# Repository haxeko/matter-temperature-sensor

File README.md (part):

# TH-SENSOR-H2 — nhiệt ẩm kế Matter over Thread (ESP32-H2, 1 × CR2450)

Thiết kế firmware và phần cứng (Rev B) cho một nhiệt ẩm kế không màn hình:

- module **ESP32-H2-MINI-1-H4S** (4 MB flash, anten PCB), **Matter over Thread** (Sleepy End Device, ICD SIT), BLE chỉ dùng khi commissioning;
- cảm biến **SHT40-AD1B-R3** trên một "lưỡi" PCB tách nhiệt, đo mỗi 60 s;
- nguồn **1 × CR2450** (holder SMT): P-MOSFET chống ngược cực, một bộ buck-boost TPS63900 ra 3.3 V, tụ đệm đầu vào 10 µF + 2 × 100 µF + 470 µF;
- một nút USER, một nút RST, một LED; không màn hình.

Firmware dùng ESP-IDF thuần (ESP-Matter chính thức, FreeRTOS, `i2c_master`, ADC có hiệu chuẩn, NVS, power management). PCB là KiCad 9 gốc, 2 lớp, 41.5 × 57.5 mm, sinh hoàn toàn bằng script trong `hardware/scripts/`.

Rev B thay Rev A (2 × CR2032, bo 72 × 58 mm) theo yêu cầu chỉ dùng một pin và bo gọn hơn; Rev A còn trong lịch sử git. Lý do chọn CR2450 thay vì một CR2032: `docs/decisions.md` D20.

Biến thể **TH-SENSOR-H2C Rev A** dùng **chip ESP32-H2FH4S rời** (QFN32) thay cho module: thạch anh 32 MHz, mạng phối hợp RF 0201, **ăng-ten in trên PCB** (inverted-F theo TI DN007), **PCB 4 lớp**, cùng kích thước bo, cùng đường nguồn và cùng firmware. File ở `hardware/chip/`, mô tả và giới hạn ở `docs/chip_variant.md`. Phần RF của biến thể này chưa đo và chưa chỉnh.

Biến thể **TH-SENSOR-H2W Rev A** dùng **module ESP32-H2-WROOM-02C-H4S** (người dùng tự mua và hàn, không có trong BOM JLC) trên một **bo 4 lớp vuông 37.6 × 37.6 mm tính cả phần ăng-ten của module nhô ra ngoài mép trên** (bo 37.6 × 31.6 mm); holder CR2450 ở mặt dưới, tụ đệm C5 là tụ tantal thấp nên cả cụm cao ≈ 12.3 mm (ước tính), một nút USER/BOOT bấm cạnh ở giữa mép trái (không có nút RST), J1 là 6 pad dán; gắn tường với cạnh có nút quay xuống đất (nút bấm từ dưới lên, lưỡi cảm biến ở góc dưới); mạch nguồn, cảm biến và firmware như Rev B. File ở `hardware/wroom/`, mô tả và giới hạn ở `docs/wroom_variant.md`.

Biến thể **TH-SENSOR-H2W-123 Rev A** là bo H2W chạy bằng **một pin CR123A** (1550 mAh) thay cho CR2450. Pin **không nằm trên bo**: bo chỉ mang phần mạch, **2 lớp**, **24.8 × 37.3 mm** (43.3 mm tính cả ăng-ten), pin đặt cạnh bo trong đế riêng và nối bằng hai dây; đặt cạnh một đế pin 18.2 × 43.3 mm thì cả cụm khoảng 43.3 × 43.3 mm. Không có tụ đệm 470 µF, có cầu chì tự phục hồi; pad nạp và test pad ở mặt sau; gắn tường với ăng-ten hướng lên, cảm biến và nút ở cạnh dưới. Theo mô hình (ƯỚC TÍNH), pin này cấp được mọi xung tải ở mọi trạng thái và cho tuổi thọ khoảng 2.3–2.6 năm. Pin sát bo chỉ cách ăng-ten khoảng 7 mm: tầm phủ CHƯA KIỂM THỬ. Chi tiết: `docs/cr123a_variant.md`.

## Trạng thái — đọc trước

Nhãn dùng trong toàn bộ repo: **ĐÃ XÁC MINH** (kiểm bằng công cụ hoặc đọc từ tài liệu gốc), **ƯỚC TÍNH** (tính toán/mô phỏng), **CHƯA KIỂM THỬ** (chưa có phần cứng).

| Hạng mục | Trạng thái | Bằng chứng |
|---|---|---|
| Firmware build: `battery`, `debug`, `battery` + lớp phủ sản xuất `prod`, `battery` + `cr123a`, `debug` + `cr123a` | ĐÃ XÁC MINH (ESP-IDF v5.5.5, 0 cảnh báo trong mã dự án; lần 2026-10-30 build sạch từ bản clone, lần 2026-11-11 build lại toàn bộ trong cây làm việc) | `docs/reports/firmware_build.md` |
| Firmware chạy trên chip (mọi profile; prod còn cần dữ liệu factory riêng từng máy) | **CHƯA KIỂM THỬ** | `docs/test_plan.md` |
| Unit test logic thuần trên host | ĐÃ XÁC MINH: 43 test, 264 kiểm tra, 0 lỗi | `docs/reports/host_tests.txt` |
| ERC schematic | ĐÃ XÁC MINH: 0 lỗi, 0 cảnh báo | `hardware/reports/erc_report.txt` |
| DRC PCB + schematic parity | ĐÃ XÁC MINH: 0 vi phạm, 0 pad chưa nối, 0 lỗi parity | `hardware/reports/drc_report.txt` |
| Pin map firmware ↔ schematic | ĐÃ XÁC MINH | `tools/check_pinmap.py`, `docs/pinmap.md` |
| Gerber, drill, BOM, CPL (định dạng JLC) | ĐÃ XÁC MINH là sinh được từ board; **chưa gửi nhà máy** | `hardware/production/` |
| Năng lượng, tuổi thọ pin | ƯỚC TÍNH — **CHƯA ĐẠT** | `docs/power_budget.md` |
| Điện, RF, cảm biến, Matter, dòng ngủ trên bo thật | **CHƯA KIỂM THỬ** (chưa có bo nào được làm) | `docs/test_plan.md` |
| OTA | **không triển khai** (`CONFIG_ENABLE_OTA_REQUESTOR=n`) | |
| Chứng nhận (Matter, FCC/CE, an toàn pin) | **không tuyên bố** | |
| Biến thể chip rời H2C: ERC, DRC + parity, pin map | ĐÃ XÁC MINH: 0 lỗi, 0 cảnh báo; 0 vi phạm, 0 pad chưa nối, 0 lỗi parity | `hardware/chip/reports/`, `tools/check_pinmap.py --variant chip` |
| Biến thể chip rời H2C: ăng-ten, phối hợp RF, thạch anh | **CHƯA KIỂM THỬ** — giá trị RF chỉ là giá trị khởi đầu, cần VNA để chỉnh | `docs/chip_variant.md` |
| Biến thể WROOM-02C H2W: ERC, DRC + parity, pin map | ĐÃ XÁC MINH: 0 lỗi, 0 cảnh báo; 0 vi phạm, 0 pad chưa nối, 0 lỗi parity | `hardware/wroom/reports/`, `tools/check_pinmap.py --variant wroom` |
| Biến thể WROOM-02C H2W: hàn tay module, ăng-ten trên bo này, ảnh hưởng của pin ở mặt dưới, hướng gắn tường | **CHƯA KIỂM THỬ** | `docs/wroom_variant.md` |
| Biến thể CR123A H2W-123: ERC, DRC + parity, pin map | ĐÃ XÁC MINH: 0 lỗi, 0 cảnh báo; 0 vi phạm, 0 pad chưa nối, 0 lỗi parity | `hardware/wroom123/reports/`, `tools/check_pinmap.py --variant wroom123` |
| Biến thể CR123A H2W-123: khả năng cấp xung và tuổi thọ pin | ƯỚC TÍNH (mô hình khớp theo đồ thị datasheet) | `hardware/analysis/results/cr123a_summary.md` |
| Biến thể CR123A H2W-123: ăng-ten khi pin cách module ~7 mm, đấu dây pin, phần trăm pin, mọi phép đo | **CHƯA KIỂM THỬ** | `docs/cr123a_variant.md` |

Chưa có đơn đặt PCB hay linh kiện nào. Chưa đo dòng, chưa ghép Matter với controller nào.

## Cảnh báo chính

1. **Thiết kế nguồn CHƯA ĐẠT** (ƯỚC TÍNH): theo mô hình, với CR2450 mới ở 25 °C mọi tải đều ổn, nhưng **khởi động và commissioning bị reset khi pin đã dùng khoảng một nửa** hoặc khi ≤ 0 °C (ngay cả pin mới). Từ giữa đời, một lần reset bất kỳ có thể làm thiết bị ngừng hoạt động tới khi thay pin; report hỏng khi pin gần cuối đời. Commission bằng pin mới ở nhiệt độ phòng. Tuổi thọ ở ~64 µA trung bình: **khoảng 0.55–0.77 năm, không phải 1–2 năm**. Điện trở xung của CR2450 là ước tính (không có số liệu công bố) và là rủi ro lớn nhất — đo trước khi làm nhiều bo (T-35). Phương án dự phòng (chưa áp dụng): `docs/power_budget.md` mục 7. Thiết kế không tự đổi sang pin khác.
2. **ESP32-H2-MINI-1-H4S tồn kho JLC = 0** (tra ngày 2026-10-29 và 2026-10-30) — chặn lắp ráp toàn bộ tại JLC; xem `docs/assembly.md`. Footprint holder CR2450 là footprint tự vẽ theo bản vẽ của nhà sản xuất: so với holder thật trước khi đặt PCB.
3. **Dữ liệu Matter thử nghiệm**: bản build mặc định dùng VID 0xFFF1 / PID 0x8000, passcode 20202021, discriminator 3840, DAC thử nghiệm — chỉ để phát triển, không bao giờ giao thiết bị như vậy.
4. **Không giả định** Apple Home, Google Home, Alexa, SmartThings, Home Assistant… sẽ chấp nhận firmware tự build này; thử lần đầu bằng `chip-tool` + OpenThread Border Router (`docs/commissioning.md`).
5. **Không bao giờ sao chép** toàn bộ flash/NVS, Thread dataset hay thông tin xác thực giữa các thiết bị.
6. **Biến thể chip rời (H2C)**: ESP32-H2FH4S tồn kho JLC = 0 (tra 2026-11-06); ăng-ten PCB và mạng phối hợp chưa mô phỏng, chưa đo — phải chỉnh bằng VNA trên bo thật; bo này không còn chứng nhận RF sẵn có của module. Xem `docs/chip_variant.md`.
7. **Biến thể WROOM-02C (H2W)**: module **không có trong BOM/CPL** (người dùng tự mua bản -H4S và hàn tay; pad tản nhiệt hàn qua lỗ 0.8 mm từ mặt dưới); holder ở **mặt dưới** (lắp ráp hai mặt hoặc tự hàn holder); dưới pin có via phủ mask. Xem `docs/wroom_variant.md`.
8. **Chỉ dùng CR2450, không sạc** (silkscreen mặt trên: "CR2450 ONLY" / "NO CHARGE" phía trên holder, dấu + và − ở hai đầu holder; mặt dưới: "CR2450 ONLY - NO CHARGE"; bản H2W: cả hai dòng và dấu +/− ở mặt dưới, cạnh holder). **Không bao giờ cấp nguồn bench khi pin đang nằm trong holder** — bo không có diode hay điện trở bảo vệ nối tiếp; xem `docs/limitations.md` mục 3.

## Sơ đồ khối

```
CR2450 ─ R1 0R ─ Q1 AO3401A ─ VIN ─ U1 TPS63900 (3.3 V) ─ VOUT ─ R21 0R ─ +3V3
 (BT1)  (đo dòng) (chống ngược)  │                         │     (đo dòng tải)
                       10 µF + 2 × 100 µF + 470 µF     22 µF + 2 × 100 µF

+3V3 ─┬─ U4 ESP32-H2-MINI-1-H4S ── I2C (GPIO10/11) ── U5 SHT40 (trên lưỡi tách nhiệt)
      ├─ U3 TPS3839K33 (2.93 V) ─ R22 ─ EN ── SW2 RST, TP6
      └─ LED (GPIO22), SW1 USER/BOOT (GPIO9), J1 debug (UART0, USB D+/D−; không có chân nguồn)
VBAT ─ 470k/470k (2N7002 đóng bằng GPIO12) ─ ADC1_CH4 (GPIO5)
```

Chi tiết và lý do chọn kiến trúc: `docs/architecture.md`, `docs/decisions.md`.

## Cấu hình linh kiện chính

| Linh kiện | Cấu hình | Nguồn |
|---|---|---|
| BT1 MYOUNG BS-24-B4AA016 | holder SMT CR2450, tiếp điểm mạ vàng; pad 1 = + (phải); footprint dự án theo bản vẽ MY-CP-0138 | datasheet LCSC C964809 |
| U1 TPS63900 | SEL = GND ⇒ VO(1) = 3.3 V (RCFG3 16.2 kΩ); RCFG1 0 Ω + RCFG2 10.5 kΩ ⇒ giới hạn dòng vào trung bình 100 mA; EN = VIN; L 2.2 µH Murata DFE201612E; vào 10 µF + 2 × 100 µF + C5 470 µF điện phân, ra 22 µF | TI SLVSET3D, bảng 7-2/7-3 |
| Q1 AO3401A | P-MOSFET chống lắp ngược cell: D phía cell, S phía VIN, G nối GND | |
| U3 TPS3839K33 | ngưỡng 2.93 V, trễ 200 ms, đẩy-kéo, qua R22 10 kΩ tới EN; C25 1 µF | TI SBVS193D |
| U5 SHT40-AD1B-R3 | I2C địa chỉ 0x44, 100 kHz, kéo lên 10 kΩ; lệnh đo độ lặp cao (0xFD), có kiểm CRC; không bật heater khi đo | Sensirion SHT4x v7.3 |
| Cầu chia pin | 470 kΩ / 470 kΩ + 22 nF từ cực + của holder, công tắc 2N7002 phía thấp; GPIO12 bật ~30 ms mỗi 6 h | |
| Y1 | 32.768 kHz Epson FC-135 (CL 12.5 pF), tụ tải 18 pF — ƯỚC TÍNH, chỉnh ở T-09 | |
| U4 | pin map đầy đủ (pad module ↔ GPIO ↔ net), chân strap, chân không dùng | `docs/pinmap.md` |

## Cấu trúc repo

```
firmware/                    dự án ESP-IDF (target esp32h2)
  main/                      app_main.cpp, app_controller.c, Kconfig.projbuild
  components/                sht40, battery, board, user_button, matter_bridge,
                             power_guard, app_config, maint_console, app_logic
  test/host/                 unit test chạy trên máy host
  sdkconfig.defaults(.battery|.debug|.prod), partitions.csv, dependencies.lock
hardware/
  scripts/                   design.py (BOM + netlist nguồn), gen_schematic.py, gen_pcb.py, gen_pcb_chip.py,
                             gen_pcb_wroom.py, gen_pcb_wroom123.py, router.py, gen_project.py, gen_reports.py,
                             gen_production.py
  kicad/                     th_sensor_h2.kicad_sch / .kicad_pcb / .kicad_pro, thư viện riêng (lib/)
  production/                Gerber + drill (zip), BOM/CPL JLC, bản vẽ lắp ráp, trở ngại sản xuất
  reports/                   ERC, DRC, routing log, tóm tắt
  renders/                   schematic.pdf, ảnh PCB (SVG, 3D PNG)
  analysis/                  power_model.py và kết quả mô phỏng
  chip/                      biến thể chip rời H2C: kicad/, production/, reports/, renders/
  wroom/                     biến thể WROOM-02C H2W: kicad/, production/, reports/, renders/
  wroom123/                  biến thể CR123A H2W-123: kicad/, production/, reports/, renders/
tools/                       check_pinmap.py, jlc_lookup.py
docs/                        tài liệu thiết kế (danh sách bên dưới), docs/reports/
```

## Firmware

### Khóa phiên bản

| Thành phần | Phiên bản | Khóa ở đâu |
|---|---|---|
| ESP-IDF | v5.5.5 (toolchain riscv32-esp-elf GCC 14.2.0, esp-14.2.0_20260121) | `firmware/main/idf_component.yml` (`idf: ==5.5.5`) |
| espressif/esp_matter | 1.6.0~1 | `idf_component.yml` (`==`), phiên bản + hash đầy đủ trong `firmware/dependencies.lock` |
| espressif/button | 4.2.1 | như trên |
| KiCad | 9.0.9 (phần cứng) | `docs/sources.md` |

Đổi bất kỳ phiên bản nào ở trên là một thay đổi thiết kế: build lại mọi cấu hình và chạy lại unit test.

### Cài toolchain

```sh
git clone -b v5.5.5 --recursive https://github.com/espressif/esp-idf.git ~/esp/esp-idf-v5.5.5
cd ~/esp/esp-idf-v5.5.5 && ./install.sh esp32h2
```

Component manager tự tải `espressif/esp_matter`, `espressif/button` và các phụ thuộc theo `firmware/dependencies.lock` ở lần build đầu (cần mạng); không cần checkout ESP-Matter riêng. Đã dùng CMake 3.28 và Ninja 1.11.

### Build, nạp, monitor

```sh
. ~/esp/esp-idf-v5.5.5/export.sh
cd firmware
P=battery                                    # hoặc: debug
idf.py -B build_$P -D SDKCONFIG=build_$P/sdkconfig \
       -D SDKCONFIG_DEFAULTS="sdkconfig.defaults;sdkconfig.defaults.$P" build
idf.py -B build_$P -D SDKCONFIG=build_$P/sdkconfig \
       -D SDKCONFIG_DEFAULTS="sdkconfig.defaults;sdkconfig.defaults.$P" -p /dev/ttyACM0 flash monitor
```

| Profile | Dùng khi | Khác biệt |
|---|---|---|
| `battery` | chạy bằng pin | log WARN, power guard bật |
| `debug` | bring-up bằng nguồn bench | log INFO, power guard tắt |
| `prod` (lớp phủ thêm sau `battery`) | sản xuất, cần dữ liệu factory riêng từng máy | build được; chạy CHƯA KIỂM THỬ — `docs/commissioning.md` mục 5 |
| `cr123a` (lớp phủ thêm sau `battery` hoặc `debug`) | bo H2W-123 chạy pin CR123A | bảng phần trăm, chuỗi IEC/dung lượng và ngưỡng pin của CR123A — `docs/cr123a_variant.md` mục 7 |

Nạp firmware qua USB-Serial/JTAG trên J1 (D+, D−, GND; 1×6 pad không lắp sẵn). J1 không có chân nguồn: bo phải chạy bằng pin, hoặc **tháo pin** rồi cấp 3.0 V (giới hạn ~150 mA) vào TP1 (VBAT, +) và TP5 (GND). Vào chế độ download bằng tay: giữ USER (SW1, GPIO9) trong khi nhấn và thả RST (SW2). Trên thiết bị đã có dữ liệu factory, **không** chạy `idf.py erase-flash` (xóa luôn phân vùng `fctry` và `esp_secure_cert`).

### Nút và LED

| Thao tác nút USER | Hành động | LED |
|---|---|---|
| Nhấn ngắn | đo ngay (tối đa 1 lần / 5 s) | 1 nháy nếu đo được, 2 nháy dài nếu lỗi |
| Nhấn 3 lần trong 2 s | mở cửa sổ commissioning 180 s, **giữ nguyên các fabric**; nếu thiết bị đã bị gỡ khỏi mọi ứng dụng thì tự khởi động lại rồi quảng bá BLE 180 s | 3 nháy |
| Giữ ≥ 10 s rồi thả | factory reset (fabric, Thread, cấu hình app; không xóa dữ liệu factory) | sáng liên tục khi đủ 10 s, 8 nháy khi chấp nhận |
| Giữ ≥ 60 s | coi là kẹt nút, không reset | tắt |

LED nháy chậm 3 lần rồi tắt hẳn ngay sau khi lắp pin hoặc reset: thiết bị vừa bị reset hai lần liên tiếp trước khi chạy đủ 10 phút (hoặc pin < 2.4 V) và đang ngủ sâu 5 phút … 4 giờ để tránh vòng lặp sụt áp. **Nhấn USER để đánh thức ngay.**

Chi tiết: `docs/architecture.md` mục 4.4.

### Console bảo trì (USB-Serial/JTAG)

`status` (cảm biến, pin, Matter/Thread, power guard, heap), `measure`, `battery`, `config` / `config set <key> <value>` (khóa: `temp_offset`, `rh_offset`, `meas_interval`, `bat_interval`, `temp_deadband`, `rh_deadband`, `led`, `tx_power`; chỉ ghi NVS khi giá trị đổi), `heater <20|110> <100|1000>` (xung heater để bảo trì; số đo lúc nóng không được phát; phép đo thường không bao giờ bật heater), `window`, `factory_reset confirm`, `reboot`. Khi USB đang nối, chip không vào light sleep (có chủ đích): rút USB khi đo dòng ngủ.

### Ghép Matter (tóm tắt, CHƯA KIỂM THỬ trên thiết bị)

1. Chuẩn bị một OpenThread Border Router và `chip-tool`; lấy active operational dataset (hex) của mạng Thread.
2. Dùng **CR2450 mới ở nhiệt độ phòng**, hoặc nguồn bench vào TP1/TP5 sau khi tháo pin (mô hình dự đoán reset khi commissioning với pin đã dùng một nửa hoặc khi lạnh).
3. Thiết bị chưa có fabric quảng bá BLE 180 s sau khi khởi động; quá thời gian thì nhấn USER 3 lần.
4. Với dữ liệu thử nghiệm của bản build mặc định:
   ```sh
   chip-tool pairing ble-thread 1 hex:<dataset> 20202021 3840
   chip-tool temperaturemeasurement read measured-value 1 1
   chip-tool relativehumiditymeasurement read measured-value 1 2
   chip-tool powersource read bat-voltage 1 0
   ```
5. Thêm hệ sinh thái thứ hai: nhấn USER 3 lần (giữ fabric cũ) hoặc dùng chức năng chia sẻ của controller đầu tiên.

Reset: nút RST = reset phần cứng (EN); factory reset = giữ USER ≥ 10 s rồi thả, hoặc `factory_reset confirm`. Chi tiết, xử lý sự cố, dữ liệu sản xuất: `docs/commissioning.md`.

### Unit test trên host

```sh
cmake -S firmware/test/host -B build/host-tests
cmake --build build/host-tests
ctest --test-dir build/host-tests --output-on-failure
```

## Phần cứng

Cần: KiCad **9.0** có module Python `pcbnew` và `kicad-cli` (đã dùng 9.0.9), Python 3 với numpy. Thư viện chuẩn của KiCad đọc từ `/usr/share/kicad/`. Symbol, footprint, mô hình 3D của module lấy từ thư viện Espressif và đã được sao vào `hardware/kicad/lib/`; chỉ cần bản checkout thư viện đó (biến `ESPRESSIF_KICAD_LIB`) khi muốn làm mới các bản sao.

Tái tạo toàn bộ, theo thứ tự (chạy từ gốc repo):

```sh
python3 hardware/scripts/gen_schematic.py    # schematic, thư viện dự án, kiểm parity với design.py
python3 hardware/scripts/gen_pcb.py          # đặt linh kiện, đi dây (router.py), đổ đồng, silkscreen (~20 s)
python3 hardware/scripts/gen_project.py      # .kicad_pro: luật thiết kế JLC 2 lớp, net class
python3 hardware/scripts/gen_reports.py      # ERC, DRC + parity, PDF/SVG/3D
python3 hardware/scripts/gen_production.py   # Gerber, drill, BOM, CPL, bản vẽ lắp ráp
python3 tools/check_pinmap.py                # board_pins.h ↔ netlist
```

Chạy lại chuỗi trên cho ra schematic và board **giống từng byte**; chỉ dấu thời gian trong Gerber/drill/báo cáo/PDF/ZIP và ảnh render 3D thay đổi.

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
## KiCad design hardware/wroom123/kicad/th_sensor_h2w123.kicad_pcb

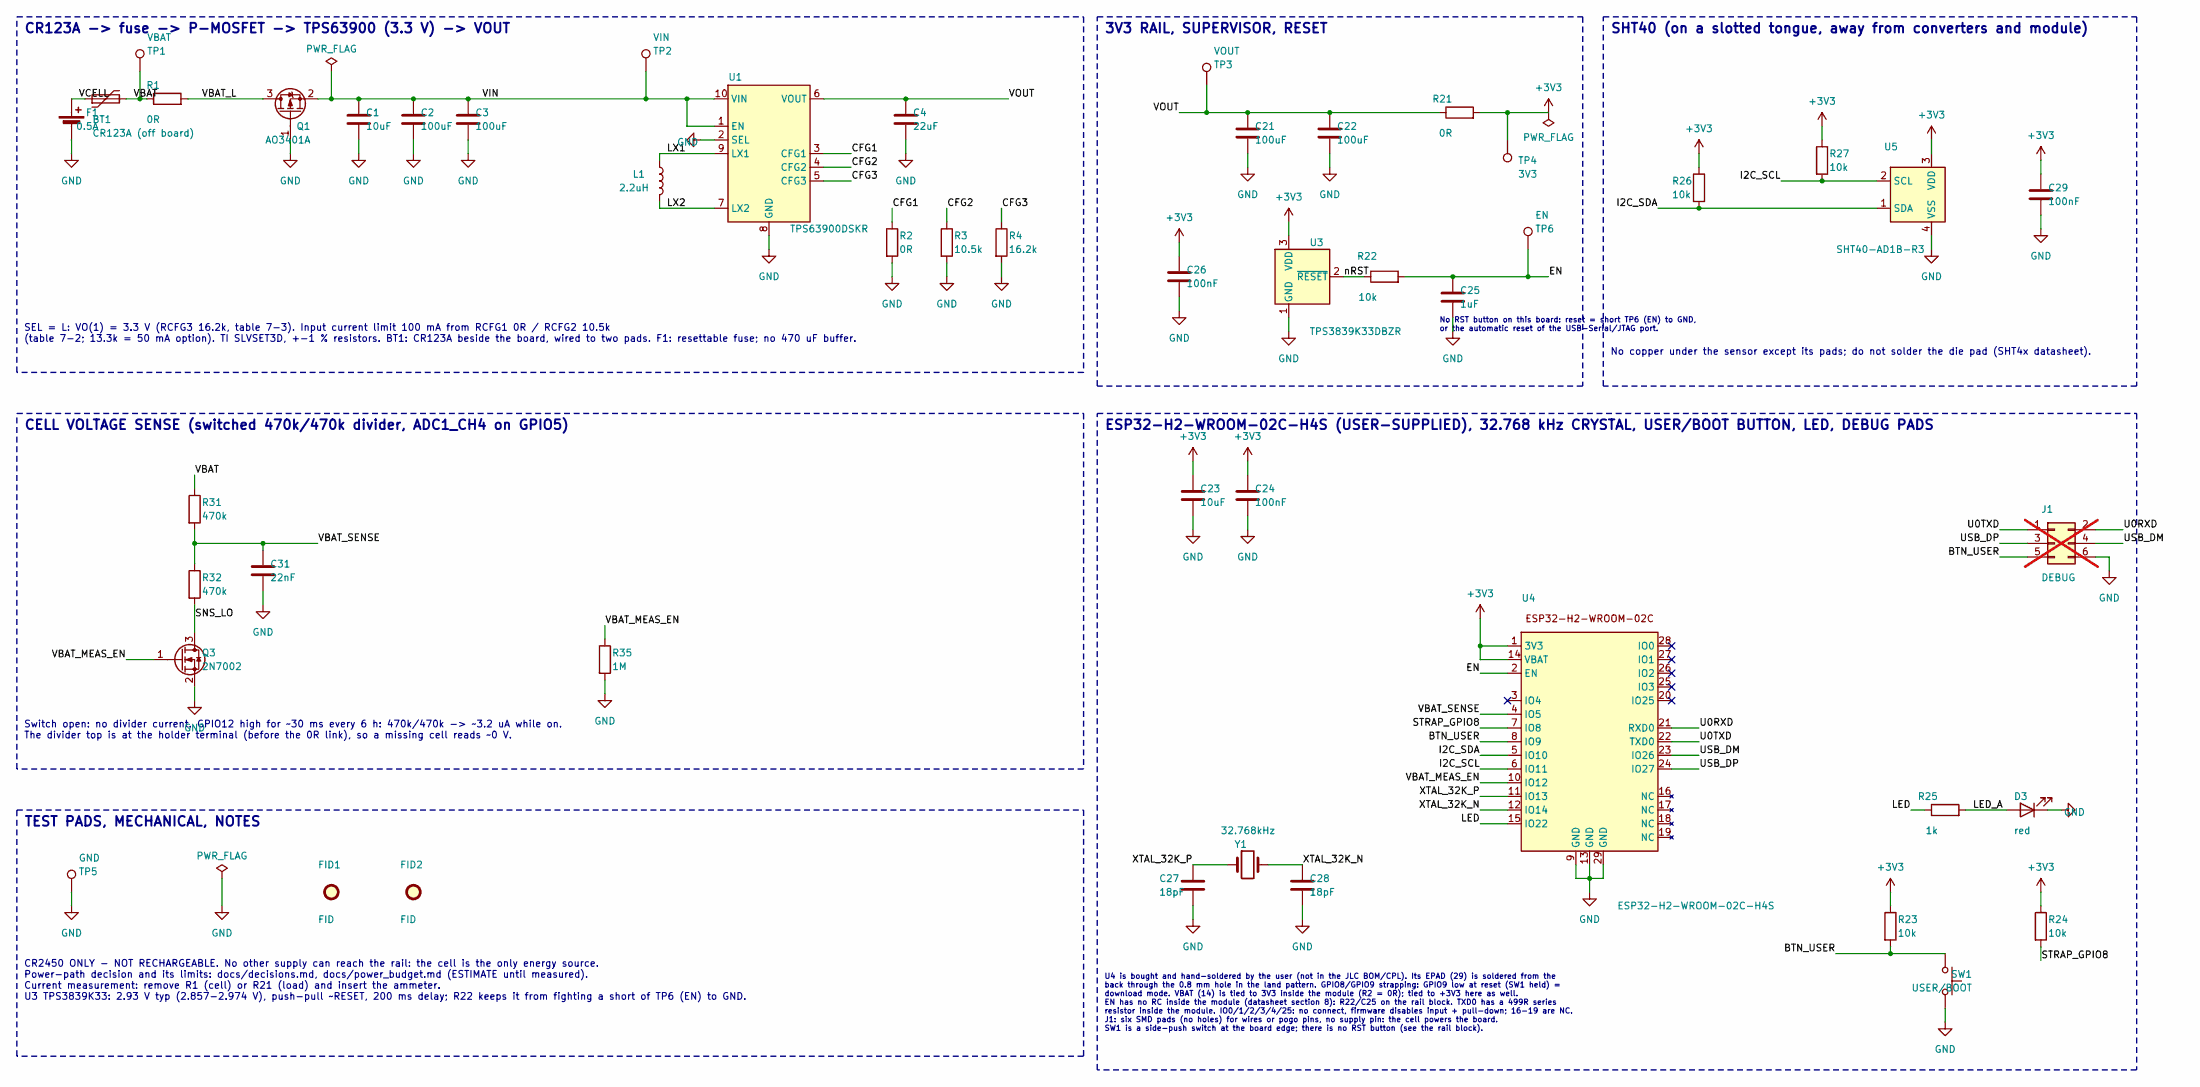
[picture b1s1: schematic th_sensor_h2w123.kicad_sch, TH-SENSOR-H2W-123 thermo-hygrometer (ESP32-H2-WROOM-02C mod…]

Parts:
BT1: CR123A (off board); BatteryWirePads_1x02_P2.54mm_D1.0mm
C1, C23: 10uF; C_0603_1608Metric; MPN CL10A106KP8NNNC; LCSC C19702
C2, C3, C21, C22: 100uF; C_1206_3216Metric; MPN CL31A107MQHNNNE; LCSC C15008
C4: 22uF; C_0805_2012Metric; MPN CL21A226MAQNNNE; LCSC C45783
C24, C26, C29: 100nF; C_0603_1608Metric; MPN CC0603KRX7R9BB104; LCSC C14663
C25: 1uF; C_0603_1608Metric; MPN CL10A105KB8NNNC; LCSC C15849
C27, C28: 18pF; C_0603_1608Metric; MPN CL10C180JB8NNNC; LCSC C1647
C31: 22nF; C_0603_1608Metric; MPN CL10B223KB8NNNC; LCSC C21122
D3: red; LED_0603_1608Metric; MPN KT-0603R; LCSC C2286
F1: 0.5A; Fuse_1206_3216Metric; MPN BSMD1206-050-6V; LCSC C883122
FID1, FID2: FID; Fiducial_1mm_Mask2mm
J1: DEBUG; TestPads_2x03_P2.54mm_SMD; not fitted
L1: 2.2uH; L_Murata_DFE201612E; MPN DFE201612E-2R2M=P2; LCSC C337893
Q1: AO3401A; SOT-23; MPN AO3401A; LCSC C15127
Q3: 2N7002; SOT-23; MPN 2N7002; LCSC C8545
R1, R21: 0R; R_0805_2012Metric; MPN 0805W8F0000T5E; LCSC C17477
R2: 0R; R_0603_1608Metric; MPN 0603WAF0000T5E; LCSC C21189
R3: 10.5k; R_0603_1608Metric; MPN 0603WAF1052T5E; LCSC C22855
R4: 16.2k; R_0603_1608Metric; MPN 0603WAF1622T5E; LCSC C22885
R22, R23, R24, R26, R27: 10k; R_0603_1608Metric; MPN 0603WAF1002T5E; LCSC C25804
R25: 1k; R_0603_1608Metric; MPN 0603WAF1001T5E; LCSC C21190
R31, R32: 470k; R_0603_1608Metric; MPN 0603WAF4703T5E; LCSC C23178
R35: 1M; R_0603_1608Metric; MPN 0603WAF1004T5E; LCSC C22935
SW1: USER/BOOT; SW_SPST_EVQP7A; MPN EVQP7A01P; LCSC C79167
TP1: VBAT; TestPoint_Pad_D1.5mm
TP2: VIN; TestPoint_Pad_D1.5mm
TP3: VOUT; TestPoint_Pad_D1.5mm
TP4: 3V3; TestPoint_Pad_D1.5mm
TP5: GND; TestPoint_Pad_D1.5mm
TP6: EN; TestPoint_Pad_D1.5mm
U1: TPS63900DSKR; WSON-10-1EP_2.5x2.5mm_P0.5mm_EP1.2x2mm; MPN TPS63900DSKR; LCSC C1518762
U3: TPS3839K33DBZR; SOT-23; MPN TPS3839K33DBZR; LCSC C96333
U4: ESP32-H2-WROOM-02C-H4S; ESP32-H2-WROOM-02C
U5: SHT40-AD1B-R3; Sensirion_DFN-4_1.5x1.5mm_P0.8mm_SHT4x_NoCentralPad; MPN SHT40-AD1B-R3; LCSC C2848306
Y1: 32.768kHz; Crystal_SMD_3215-2Pin_3.2x1.5mm; MPN Q13FC13500004; LCSC C32346

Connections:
+3V3: C23.1, C24.1, C26.1, C29.1, R21.2, R23.1, R24.1, R26.1, R27.1, TP4.1, U3.3 (VDD), U4.1 (3V3), U4.14 (VBAT), U5.3 (VDD)
/BTN_USER: J1.5, R23.2, SW1.1, U4.8 (IO9)
/CFG1: R2.1, U1.3 (CFG1)
/CFG2: R3.1, U1.4 (CFG2)
/CFG3: R4.1, U1.5 (CFG3)
/EN: C25.1, R22.2, TP6.1, U4.2 (EN)
/I2C_SCL: R27.2, U4.6 (IO11), U5.2 (SCL)
/I2C_SDA: R26.2, U4.5 (IO10), U5.1 (SDA)
/LED: R25.1, U4.15 (IO22)
/LED_A: D3.2 (A), R25.2
/LX1: L1.1, U1.9 (LX1)
/LX2: L1.2, U1.7 (LX2)
/SNS_LO: Q3.3 (D), R32.2
/STRAP_GPIO8: R24.2, U4.7 (IO8)
/U0RXD: J1.2, U4.21 (RXD0)
/U0TXD: J1.1, U4.22 (TXD0)
/USB_DM: J1.4, U4.23 (IO26)
/USB_DP: J1.3, U4.24 (IO27)
/VBAT: F1.2, R1.1, R31.1, TP1.1
/VBAT_L: Q1.3 (D), R1.2
/VBAT_MEAS_EN: Q3.1 (G), R35.1, U4.10 (IO12)
/VBAT_SENSE: C31.1, R31.2, R32.1, U4.4 (IO5)
/VCELL: BT1.1 (+), F1.1
/VIN: C1.1, C2.1, C3.1, Q1.2 (S), TP2.1, U1.1 (EN), U1.10 (VIN)
/VOUT: C4.1, C21.1, C22.1, R21.1, TP3.1, U1.6 (VOUT)
/XTAL_32K_N: C28.1, U4.12 (IO14), Y1.2
/XTAL_32K_P: C27.1, U4.11 (IO13), Y1.1
/nRST: R22.1, U3.2 (~RESET)
GND: BT1.2 (-), C1.2, C2.2, C3.2, C4.2, C21.2, C22.2, C23.2, C24.2, C25.2, C26.2, C27.2, C28.2, C29.2, C31.2, D3.1 (K), J1.6, Q1.1 (G), Q3.2 (S), R2.2, R3.2, R4.2, R35.2, SW1.2, TP5.1, U1.2 (SEL), U1.8 (GND), U1.11 (GND), U3.1 (GND), U4.9 (GND), U4.13 (GND), U4.29 (GND), U5.4 (VSS)

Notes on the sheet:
CR123A -> fuse -> P-MOSFET -> TPS63900 (3.3 V) -> VOUT
SEL = L: VO(1) = 3.3 V (RCFG3 16.2k, table 7-3). Input current limit 100 mA from RCFG1 0R / RCFG2 10.5k (table 7-2; 13.3k = 50 mA option). TI SLVSET3D, +-1 % resistors. BT1: CR123A beside the board, wired to two pads. F1: resettable fuse; no 470 uF buffer.
3V3 RAIL, SUPERVISOR, RESET
No RST button on this board: reset = short TP6 (EN) to GND, or the automatic reset of the USB-Serial/JTAG port.
ESP32-H2-WROOM-02C-H4S (USER-SUPPLIED), 32.768 kHz CRYSTAL, USER/BOOT BUTTON, LED, DEBUG PADS
U4 is bought and hand-soldered by the user (not in the JLC BOM/CPL). Its EPAD (29) is soldered from the back through the 0.8 mm hole in the land pattern. GPIO8/GPIO9 strapping: GPIO9 low at reset (SW1 held) = download mode. VBAT (14) is tied to 3V3 inside the module (R2 = 0R); tied to +3V3 here as 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
SHT40 (on a slotted tongue, away from converters and module)
No copper under the sensor except its pads; do not solder the die pad (SHT4x datasheet).
CELL VOLTAGE SENSE (switched 470k/470k divider, ADC1_CH4 on GPIO5)
Switch open: no divider current. GPIO12 high for ~30 ms every 6 h: 470k/470k -> ~3.2 uA while on. The divider top is at the holder terminal (before the 0R link), so a missing cell reads ~0 V.
TEST PADS, MECHANICAL, NOTES
CR2450 ONLY - NOT RECHARGEABLE. No other supply can reach the rail: the cell is the only energy source. Power-path decision and its limits: docs/decisions.md, docs/power_budget.md (ESTIMATE until measured). Current measurement: remove R1 (cell) or R21 (load) and insert the ammeter. U3 TPS3839K33: 2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

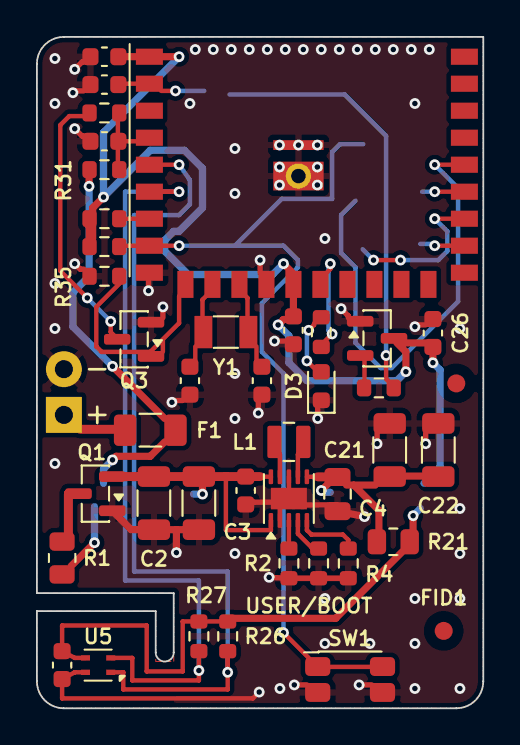
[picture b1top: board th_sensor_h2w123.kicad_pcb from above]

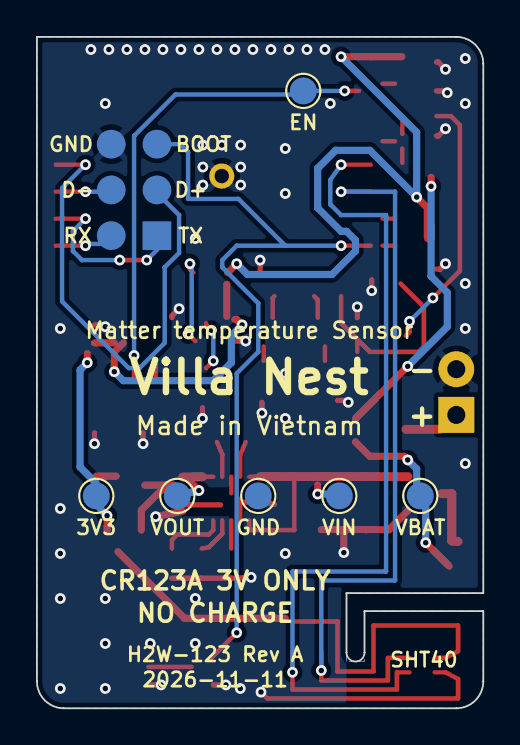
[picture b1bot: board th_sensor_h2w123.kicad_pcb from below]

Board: 2 copper layers, 24.8 x 37.3 mm, 49 parts (7 on the bottom side), 29 nets.

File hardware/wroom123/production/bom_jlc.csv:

Comment,Designator,Footprint,LCSC Part #,Manufacturer,MPN,Qty,JLC library,JLC stock,Stock checked
10uF 10V X5R 0603,"C1,C23",C_0603_1608Metric,C19702,Samsung,CL10A106KP8NNNC,2,Basic,9600441,2026-11-11 02:15 UTC
100uF 6.3V X5R 1206,"C2,C3,C21,C22",C_1206_3216Metric,C15008,Samsung,CL31A107MQHNNNE,4,Basic,1605881,2026-11-11 02:15 UTC
1uF 0603,C25,C_0603_1608Metric,C15849,Samsung,CL10A105KB8NNNC,1,Basic,12307470,2026-11-11 02:15 UTC
100nF 0603,"C24,C26,C29",C_0603_1608Metric,C14663,YAGEO,CC0603KRX7R9BB104,3,Basic,36346845,2026-11-11 02:15 UTC
18pF 50V C0G 0603,"C27,C28",C_0603_1608Metric,C1647,Samsung,CL10C180JB8NNNC,2,Basic,394613,2026-11-11 02:15 UTC
22nF 0603,C31,C_0603_1608Metric,C21122,Samsung,CL10B223KB8NNNC,1,Basic,1023968,2026-11-11 02:15 UTC
22uF 25V X5R 0805,C4,C_0805_2012Metric,C45783,Samsung,CL21A226MAQNNNE,1,Basic,3818412,2026-11-11 02:15 UTC
red,D3,LED_0603_1608Metric,C2286,KENTO,KT-0603R,1,Basic,6230550,2026-11-11 02:15 UTC
0.5A PTC 6V hold 0.5A trip 1A 1206,F1,Fuse_1206_3216Metric,C883122,BHFUSE,BSMD1206-050-6V,1,Extended,42372,2026-11-11 02:15 UTC
2.2uH,L1,L_Murata_DFE201612E,C337893,Murata,DFE201612E-2R2M=P2,1,Extended,34245,2026-11-11 02:15 UTC
AO3401A,Q1,SOT-23,C15127,Alpha & Omega,AO3401A,1,Basic,1631248,2026-11-11 02:15 UTC
2N7002,Q3,SOT-23,C8545,JSCJ,2N7002,1,Basic,5856189,2026-11-11 02:15 UTC
0R 1% 0805,"R1,R21",R_0805_2012Metric,C17477,UNI-ROYAL,0805W8F0000T5E,2,Basic,4041504,2026-11-11 02:15 UTC
0R 1% 0603,R2,R_0603_1608Metric,C21189,UNI-ROYAL,0603WAF0000T5E,1,Basic,18400501,2026-11-11 02:15 UTC
10k 1% 0603,"R22,R23,R24,R26,R27",R_0603_1608Metric,C25804,UNI-ROYAL,0603WAF1002T5E,5,Basic,45074595,2026-11-11 02:15 UTC
1k 1% 0603,R25,R_0603_1608Metric,C21190,UNI-ROYAL,0603WAF1001T5E,1,Basic,26681181,2026-11-11 02:15 UTC
10.5k 1% 100ppm 0603,R3,R_0603_1608Metric,C22855,UNI-ROYAL,0603WAF1052T5E,1,Extended,97693,2026-11-11 02:15 UTC
470k 1% 0603,"R31,R32",R_0603_1608Metric,C23178,UNI-ROYAL,0603WAF4703T5E,2,Basic,889239,2026-11-11 02:15 UTC
1M 1% 0603,R35,R_0603_1608Metric,C22935,UNI-ROYAL,0603WAF1004T5E,1,Basic,4026565,2026-11-11 02:15 UTC
16.2k 1% 100ppm 0603,R4,R_0603_1608Metric,C22885,UNI-ROYAL,0603WAF1622T5E,1,Extended,49276,2026-11-11 02:15 UTC
USER/BOOT,SW1,SW_SPST_EVQP7A,C79167,PANASONIC,EVQP7A01P,1,Extended,3478,2026-11-11 02:15 UTC
TPS63900DSKR,U1,WSON-10-1EP_2.5x2.5mm_P0.5mm_EP1.2x2mm,C1518762,Texas Instruments,TPS63900DSKR,1,Extended,8237,2026-11-11 02:15 UTC
TPS3839K33DBZR,U3,SOT-23,C96333,Texas Instruments,TPS3839K33DBZR,1,Extended,733,2026-11-11 02:15 UTC
SHT40-AD1B-R3,U5,Sensirion_DFN-4_1.5x1.5mm_P0.8mm_SHT4x_NoCentralPad,C2848306,Sensirion,SHT40-AD1B-R3,1,Extended,13484,2026-11-11 02:15 UTC
"32.768kHz CL 12.5pF, ESR<=70k, 20ppm",Y1,Crystal_SMD_3215-2Pin_3.2x1.5mm,C32346,Seiko Epson,Q13FC13500004,1,Basic,399955,2026-11-11 02:15 UTC

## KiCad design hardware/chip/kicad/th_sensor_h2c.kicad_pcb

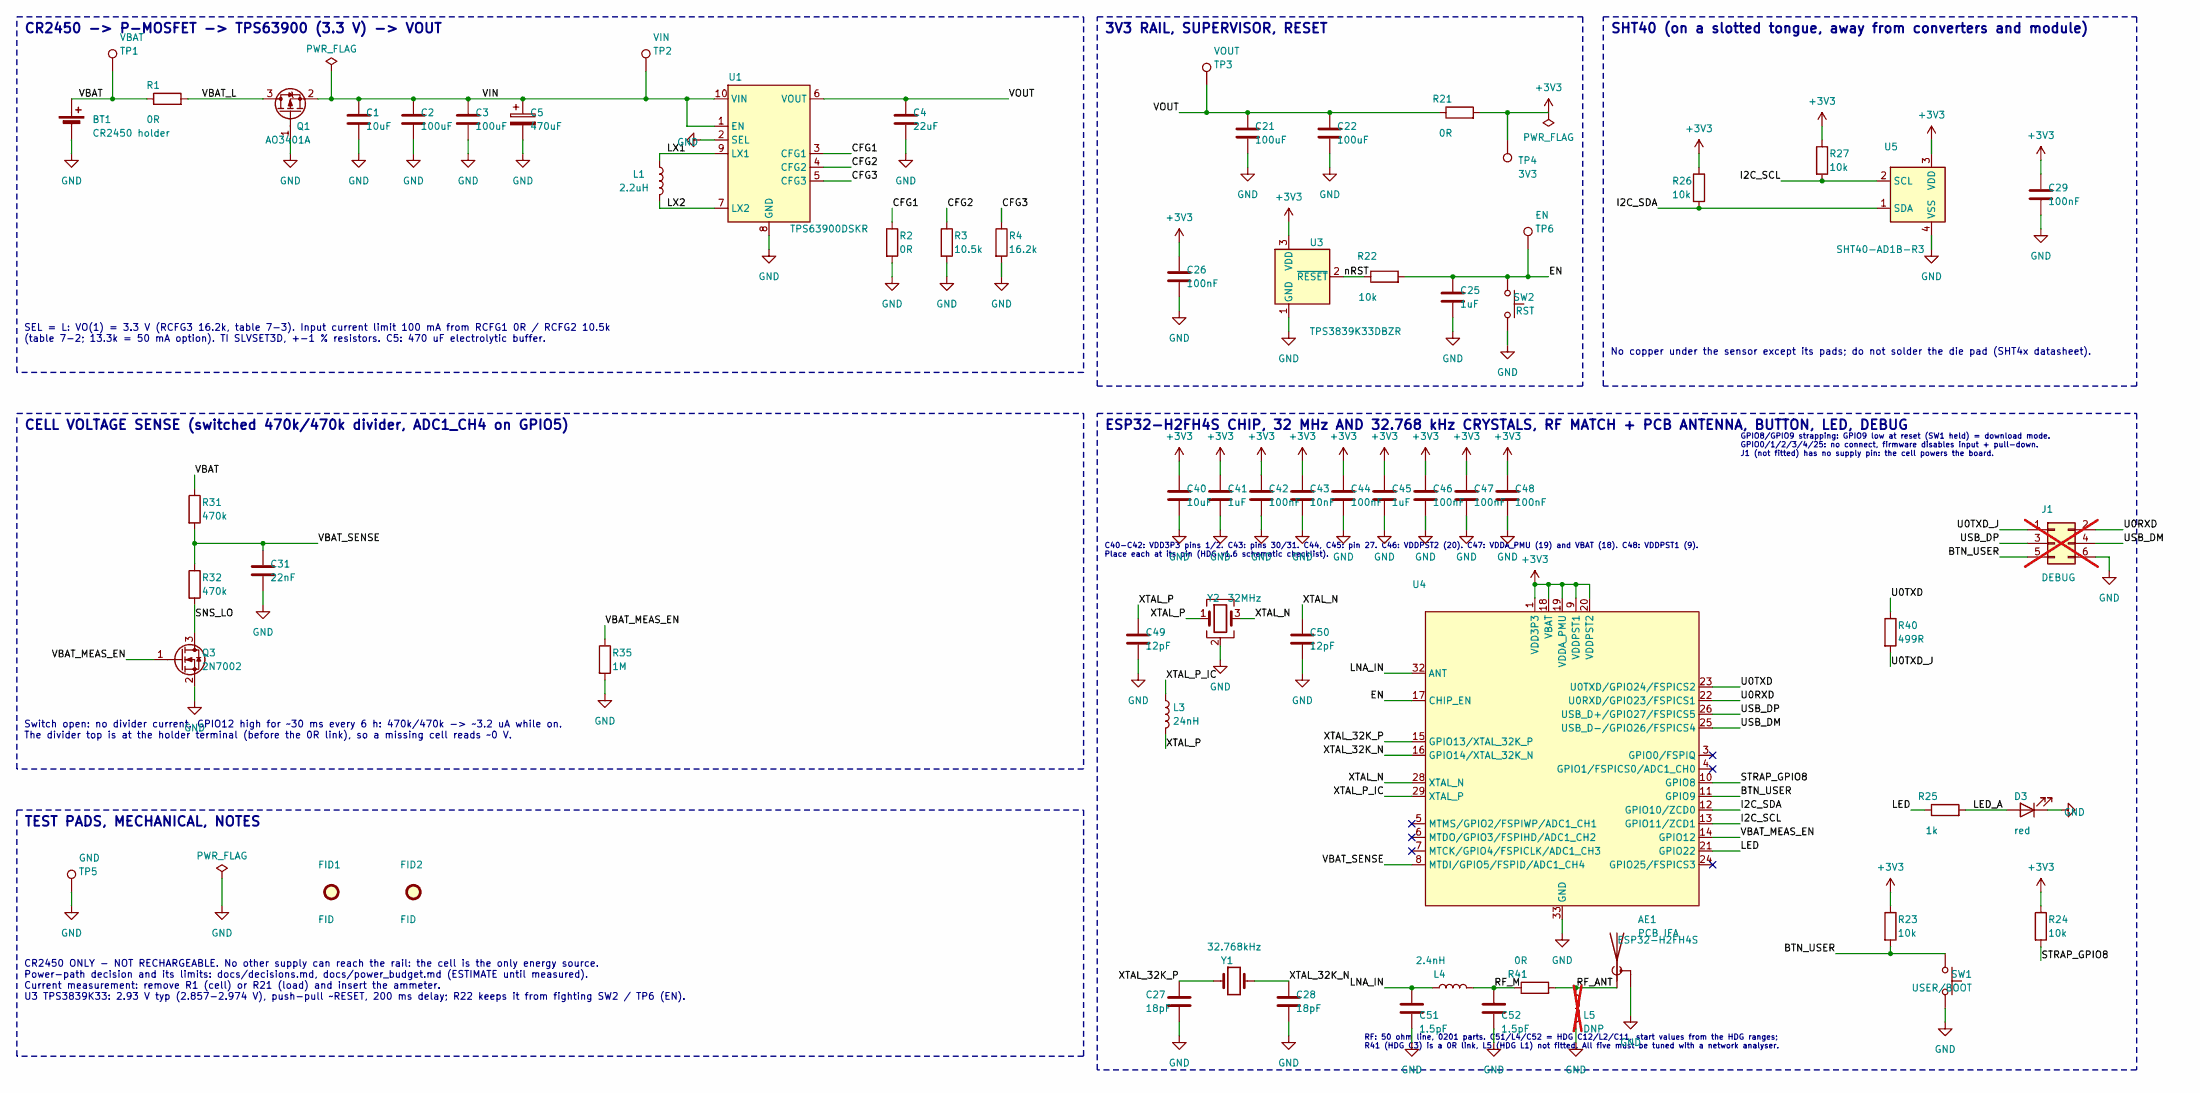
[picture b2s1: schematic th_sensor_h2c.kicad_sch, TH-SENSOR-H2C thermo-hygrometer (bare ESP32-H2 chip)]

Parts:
AE1: PCB IFA; Antenna_TI_DN007_IFA_2.4GHz_Mirrored
BT1: CR2450 holder; BatteryHolder_MYOUNG_BS-24-B4AA016_1x2450; MPN BS-24-B4AA016; LCSC C964809
C1, C40: 10uF; C_0603_1608Metric; MPN CL10A106KP8NNNC; LCSC C19702
C2, C3, C21, C22: 100uF; C_1206_3216Metric; MPN CL31A107MQHNNNE; LCSC C15008
C4: 22uF; C_0805_2012Metric; MPN CL21A226MAQNNNE; LCSC C45783
C5: 470uF; CP_Elec_6.3x7.7; MPN RVT470UF6.3V67RV0038; LCSC C2901342
C25, C41, C45: 1uF; C_0603_1608Metric; MPN CL10A105KB8NNNC; LCSC C15849
C26, C29, C42, C44, C46, C47, C48: 100nF; C_0603_1608Metric; MPN CC0603KRX7R9BB104; LCSC C14663
C27, C28: 18pF; C_0603_1608Metric; MPN CL10C180JB8NNNC; LCSC C1647
C31: 22nF; C_0603_1608Metric; MPN CL10B223KB8NNNC; LCSC C21122
C43: 10nF; C_0603_1608Metric; MPN 0603B103K500NT; LCSC C57112
C49, C50: 12pF; C_0603_1608Metric; MPN CL10C120JB8NNNC; LCSC C38523
C51, C52: 1.5pF; C_0201_0603Metric; MPN GRM0335C1H1R5BA01D; LCSC C161414
D3: red; LED_0603_1608Metric; MPN KT-0603R; LCSC C2286
FID1, FID2: FID; Fiducial_1mm_Mask2mm
J1: DEBUG; PinHeader_2x03_P2.54mm_Vertical; not fitted
L1: 2.2uH; L_Murata_DFE201612E; MPN DFE201612E-2R2M=P2; LCSC C337893
L3: 24nH; L_0603_1608Metric; MPN LQW18AN24NG00D; LCSC C162644
L4: 2.4nH; L_0201_0603Metric; MPN LQP03TN2N4B02D; LCSC C98042
L5: DNP; L_0201_0603Metric; not fitted
Q1: AO3401A; SOT-23; MPN AO3401A; LCSC C15127
Q3: 2N7002; SOT-23; MPN 2N7002; LCSC C8545
R1, R21: 0R; R_0805_2012Metric; MPN 0805W8F0000T5E; LCSC C17477
R2: 0R; R_0603_1608Metric; MPN 0603WAF0000T5E; LCSC C21189
R3: 10.5k; R_0603_1608Metric; MPN 0603WAF1052T5E; LCSC C22855
R4: 16.2k; R_0603_1608Metric; MPN 0603WAF1622T5E; LCSC C22885
R22, R23, R24, R26, R27: 10k; R_0603_1608Metric; MPN 0603WAF1002T5E; LCSC C25804
R25: 1k; R_0603_1608Metric; MPN 0603WAF1001T5E; LCSC C21190
R31, R32: 470k; R_0603_1608Metric; MPN 0603WAF4703T5E; LCSC C23178
R35: 1M; R_0603_1608Metric; MPN 0603WAF1004T5E; LCSC C22935
R40: 499R; R_0603_1608Metric; MPN 0603WAF4990T5E; LCSC C23065
R41: 0R; R_0201_0603Metric; MPN 0201WMF0000TEE; LCSC C473473
SW1: USER/BOOT; SW_Push_1P1T_XKB_TS-1187A; MPN TS-1187A-B-A-B; LCSC C318884
SW2: RST; SW_Push_1P1T_XKB_TS-1187A; MPN TS-1187A-B-A-B; LCSC C318884
TP1: VBAT; TestPoint_Pad_D1.5mm
TP2: VIN; TestPoint_Pad_D1.5mm
TP3: VOUT; TestPoint_Pad_D1.5mm
TP4: 3V3; TestPoint_Pad_D1.5mm
TP5: GND; TestPoint_Pad_D1.5mm
TP6: EN; TestPoint_Pad_D1.5mm
U1: TPS63900DSKR; WSON-10-1EP_2.5x2.5mm_P0.5mm_EP1.2x2mm; MPN TPS63900DSKR; LCSC C1518762
U3: TPS3839K33DBZR; SOT-23; MPN TPS3839K33DBZR; LCSC C96333
U4: ESP32-H2FH4S; QFN-32-1EP_4x4mm_P0.4mm_EP2.9x2.9mm; MPN ESP32-H2FH4S; LCSC C50392664
U5: SHT40-AD1B-R3; Sensirion_DFN-4_1.5x1.5mm_P0.8mm_SHT4x_NoCentralPad; MPN SHT40-AD1B-R3; LCSC C2848306
Y1: 32.768kHz; Crystal_SMD_3215-2Pin_3.2x1.5mm; MPN Q13FC13500004; LCSC C32346
Y2: 32MHz; Crystal_SMD_3225-4Pin_3.2x2.5mm; MPN X322532MLB4SI; LCSC C5210649

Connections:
+3V3: C26.1, C29.1, C40.1, C41.1, C42.1, C43.1, C44.1, C45.1, C46.1, C47.1, C48.1, R21.2, R23.1, R24.1, R26.1, R27.1, TP4.1, U3.3 (VDD), U4.1 (VDD3P3), U4.2 (VDD3P3), U4.9 (VDDPST1), U4.18 (VBAT), U4.19 (VDDA_PMU), U4.20 (VDDPST2), U4.27 (VDD3P3), U4.30 (VDD3P3), U4.31 (VDD3P3), U5.3 (VDD)
/BTN_USER: J1.5, R23.2, SW1.1, U4.11 (GPIO9)
/CFG1: R2.1, U1.3 (CFG1)
/CFG2: R3.1, U1.4 (CFG2)
/CFG3: R4.1, U1.5 (CFG3)
/EN: C25.1, R22.2, SW2.1, TP6.1, U4.17 (CHIP_EN)
/I2C_SCL: R27.2, U4.13 (GPIO11/ZCD1), U5.2 (SCL)
/I2C_SDA: R26.2, U4.12 (GPIO10/ZCD0), U5.1 (SDA)
/LED: R25.1, U4.21 (GPIO22)
/LED_A: D3.2 (A), R25.2
/LNA_IN: C51.1, L4.1, U4.32 (ANT)
/LX1: L1.1, U1.9 (LX1)
/LX2: L1.2, U1.7 (LX2)
/RF_ANT: AE1.1 (A), L5.1, R41.2
/RF_M: C52.1, L4.2, R41.1
/SNS_LO: Q3.3 (D), R32.2
/STRAP_GPIO8: R24.2, U4.10 (GPIO8)
/U0RXD: J1.2, U4.22 (U0RXD/GPIO23/FSPICS1)
/U0TXD: R40.1, U4.23 (U0TXD/GPIO24/FSPICS2)
/U0TXD_J: J1.1, R40.2
/USB_DM: J1.4, U4.25 (USB_D-/GPIO26/FSPICS4)
/USB_DP: J1.3, U4.26 (USB_D+/GPIO27/FSPICS5)
/VBAT: BT1.1 (+), R1.1, R31.1, TP1.1
/VBAT_L: Q1.3 (D), R1.2
/VBAT_MEAS_EN: Q3.1 (G), R35.1, U4.14 (GPIO12)
/VBAT_SENSE: C31.1, R31.2, R32.1, U4.8 (MTDI/GPIO5/FSPID/ADC1_CH4)
/VIN: C1.1, C2.1, C3.1, C5.1, Q1.2 (S), TP2.1, U1.1 (EN), U1.10 (VIN)
/VOUT: C4.1, C21.1, C22.1, R21.1, TP3.1, U1.6 (VOUT)
/XTAL_32K_N: C28.1, U4.16 (GPIO14/XTAL_32K_N), Y1.2
/XTAL_32K_P: C27.1, U4.15 (GPIO13/XTAL_32K_P), Y1.1
/XTAL_N: C50.1, U4.28 (XTAL_N), Y2.3
/XTAL_P: C49.1, L3.2, Y2.1
/XTAL_P_IC: L3.1, U4.29 (XTAL_P)
/nRST: R22.1, U3.2 (~RESET)
GND: AE1.2 (Shield), BT1.2 (-), C1.2, C2.2, C3.2, C4.2, C5.2, C21.2, C22.2, C25.2, C26.2, C27.2, C28.2, C29.2, C31.2, C40.2, C41.2, C42.2, C43.2, C44.2, C45.2, C46.2, C47.2, C48.2, C49.2, C50.2, C51.2, C52.2, D3.1 (K), J1.6, L5.2, Q1.1 (G), Q3.2 (S), R2.2, R3.2, R4.2, R35.2, SW1.2, SW2.2, TP5.1, U1.2 (SEL), U1.8 (GND), U1.11 (GND), U3.1 (GND), U4.33 (GND), U5.4 (VSS), Y2.2 (G), Y2.4 (G)

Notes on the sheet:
CR2450 -> P-MOSFET -> TPS63900 (3.3 V) -> VOUT
SEL = L: VO(1) = 3.3 V (RCFG3 16.2k, table 7-3). Input current limit 100 mA from RCFG1 0R / RCFG2 10.5k (table 7-2; 13.3k = 50 mA option). TI SLVSET3D, +-1 % resistors. C5: 470 uF electrolytic buffer.
3V3 RAIL, SUPERVISOR, RESET
ESP32-H2FH4S CHIP, 32 MHz AND 32.768 kHz CRYSTALS, RF MATCH + PCB ANTENNA, BUTTON, LED, DEBUG
C40-C42: VDD3P3 pins 1/2. C43: pins 30/31. C44, C45: pin 27. C46: VDDPST2 (20). C47: VDDA_PMU (19) and VBAT (18). C48: VDDPST1 (9). Place each at its pin (HDG v1.6 schematic checklist).
RF: 50 ohm line, 0201 parts. C51/L4/C52 = HDG C12/L2/C11, start values from the HDG ranges; R41 (HDG C3) is a 0R link, L5 (HDG L1) not fitted. All five must be tuned with a network analyser.
GPIO8/GPIO9 strapping: GPIO9 low at reset (SW1 held) = download mode. GPIO0/1/2/3/4/25: no connect, firmware disables input + pull-down. J1 (not fitted) has no supply pin: the cell powers the board.
SHT40 (on a slotted tongue, away from converters and module)
No copper under the sensor except its pads; do not solder the die pad (SHT4x datasheet).
CELL VOLTAGE SENSE (switched 470k/470k divider, ADC1_CH4 on GPIO5)
Switch open: no divider current. GPIO12 high for ~30 ms every 6 h: 470k/470k -> ~3.2 uA while on. The divider top is at the holder terminal (before the 0R link), so a missing cell reads ~0 V.
TEST PADS, MECHANICAL, NOTES
CR2450 ONLY - NOT RECHARGEABLE. No other supply can reach the rail: the cell is the only energy source. Power-path decision and its limits: docs/decisions.md, docs/power_budget.md (ESTIMATE until measured). Current measurement: remove R1 (cell) or R21 (load) and insert the ammeter. U3 TPS3839K33: 2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

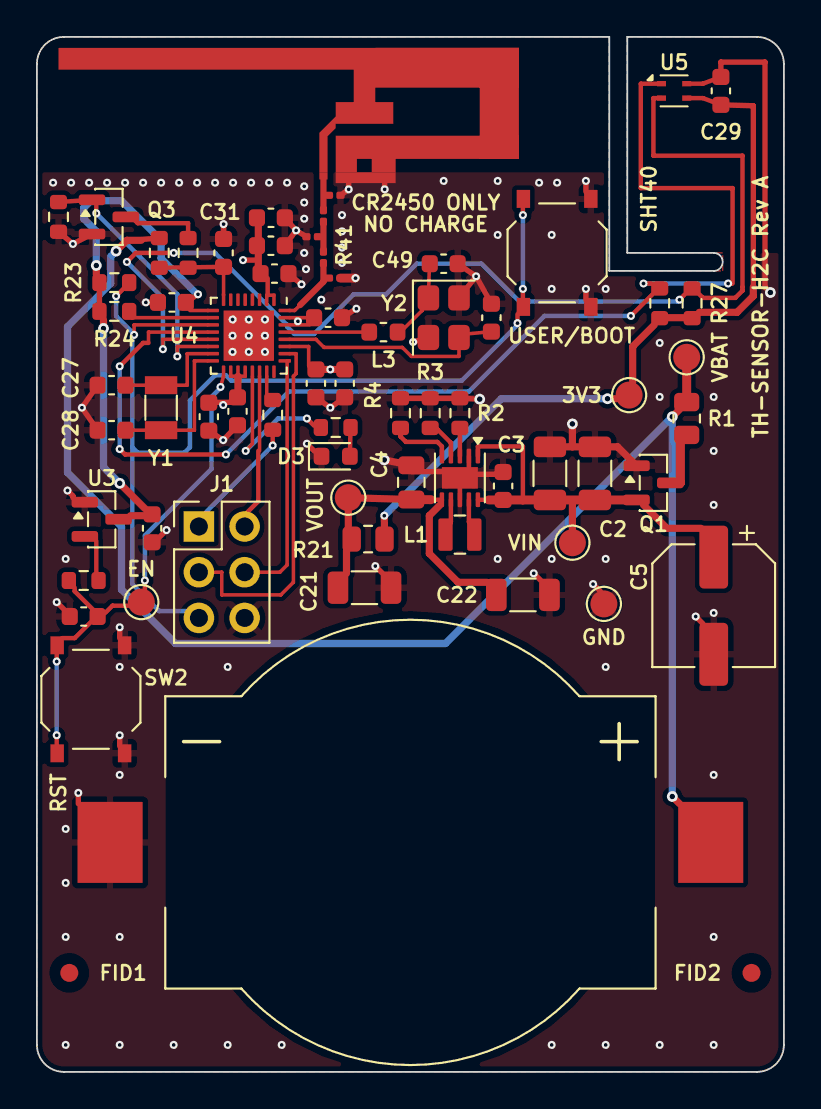
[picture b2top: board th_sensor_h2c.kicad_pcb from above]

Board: 4 copper layers, 41.5 x 57.5 mm, 68 parts (0 on the bottom side), 35 nets.

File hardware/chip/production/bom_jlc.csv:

Comment,Designator,Footprint,LCSC Part #,Manufacturer,MPN,Qty,JLC library,JLC stock,Stock checked
CR2450 holder,BT1,BatteryHolder_MYOUNG_BS-24-B4AA016_1x2450,C964809,MYOUNG,BS-24-B4AA016,1,Extended,2042,2026-11-06 07:12 UTC
10uF 10V X5R 0603,"C1,C40",C_0603_1608Metric,C19702,Samsung,CL10A106KP8NNNC,2,Basic,10594453,2026-11-06 07:12 UTC
100uF 6.3V X5R 1206,"C2,C3,C21,C22",C_1206_3216Metric,C15008,Samsung,CL31A107MQHNNNE,4,Basic,1549418,2026-11-06 07:12 UTC
1uF 0603,"C25,C41,C45",C_0603_1608Metric,C15849,Samsung,CL10A105KB8NNNC,3,Basic,11480539,2026-11-06 07:12 UTC
100nF 0603,"C26,C29,C42,C44,C46,C47,C48",C_0603_1608Metric,C14663,YAGEO,CC0603KRX7R9BB104,7,Basic,35206825,2026-11-06 07:12 UTC
18pF 50V C0G 0603,"C27,C28",C_0603_1608Metric,C1647,Samsung,CL10C180JB8NNNC,2,Basic,416376,2026-11-06 07:12 UTC
22nF 0603,C31,C_0603_1608Metric,C21122,Samsung,CL10B223KB8NNNC,1,Basic,818118,2026-11-06 07:12 UTC
22uF 25V X5R 0805,C4,C_0805_2012Metric,C45783,Samsung,CL21A226MAQNNNE,1,Basic,3430955,2026-11-06 07:12 UTC
10nF 0603,C43,C_0603_1608Metric,C57112,FH,0603B103K500NT,1,Basic,5066614,2026-11-06 07:12 UTC
12pF 50V C0G 0603,"C49,C50",C_0603_1608Metric,C38523,Samsung,CL10C120JB8NNNC,2,Basic,523977,2026-11-06 07:12 UTC
470uF 6.3V Al electrolytic 6.3x7.7mm,C5,CP_Elec_6.3x7.7,C2901342,KNSCHA,RVT470UF6.3V67RV0038,1,Extended,1996,2026-11-06 07:12 UTC
1.5pF 50V C0G 0201 +-0.1pF,"C51,C52",C_0201_0603Metric,C161414,Murata,GRM0335C1H1R5BA01D,2,Extended,36181,2026-11-06 07:12 UTC
red,D3,LED_0603_1608Metric,C2286,KENTO,KT-0603R,1,Basic,6609942,2026-11-06 07:12 UTC
2.2uH,L1,L_Murata_DFE201612E,C337893,Murata,DFE201612E-2R2M=P2,1,Extended,35754,2026-11-06 07:12 UTC
24nH 2% 0603,L3,L_0603_1608Metric,C162644,Murata,LQW18AN24NG00D,1,Extended,8016,2026-11-06 07:12 UTC
2.4nH 0201 +-0.1nH,L4,L_0201_0603Metric,C98042,Murata,LQP03TN2N4B02D,1,Extended,85855,2026-11-06 07:12 UTC
AO3401A,Q1,SOT-23,C15127,Alpha & Omega,AO3401A,1,Basic,1617940,2026-11-06 07:12 UTC
2N7002,Q3,SOT-23,C8545,JSCJ,2N7002,1,Basic,4206673,2026-11-06 07:12 UTC
0R 1% 0805,"R1,R21",R_0805_2012Metric,C17477,UNI-ROYAL,0805W8F0000T5E,2,Basic,4379751,2026-11-06 07:12 UTC
0R 1% 0603,R2,R_0603_1608Metric,C21189,UNI-ROYAL,0603WAF0000T5E,1,Basic,19312772,2026-11-06 07:12 UTC
10k 1% 0603,"R22,R23,R24,R26,R27",R_0603_1608Metric,C25804,UNI-ROYAL,0603WAF1002T5E,5,Basic,42908910,2026-11-06 07:12 UTC
1k 1% 0603,R25,R_0603_1608Metric,C21190,UNI-ROYAL,0603WAF1001T5E,1,Basic,27593843,2026-11-06 07:12 UTC
10.5k 1% 100ppm 0603,R3,R_0603_1608Metric,C22855,UNI-ROYAL,0603WAF1052T5E,1,Extended,100693,2026-11-06 07:12 UTC
470k 1% 0603,"R31,R32",R_0603_1608Metric,C23178,UNI-ROYAL,0603WAF4703T5E,2,Basic,940587,2026-11-06 07:12 UTC
1M 1% 0603,R35,R_0603_1608Metric,C22935,UNI-ROYAL,0603WAF1004T5E,1,Basic,4471064,2026-11-06 07:12 UTC
16.2k 1% 100ppm 0603,R4,R_0603_1608Metric,C22885,UNI-ROYAL,0603WAF1622T5E,1,Extended,51134,2026-11-06 07:12 UTC
499R 1% 0603,R40,R_0603_1608Metric,C23065,UNI-ROYAL,0603WAF4990T5E,1,Extended,453707,2026-11-06 07:12 UTC
0R 0201,R41,R_0201_0603Metric,C473473,UNI-ROYAL,0201WMF0000TEE,1,Extended,3094110,2026-11-06 07:12 UTC
USER/BOOT,SW1,SW_Push_1P1T_XKB_TS-1187A,C318884,XKB,TS-1187A-B-A-B,1,Basic,951682,2026-11-06 07:12 UTC
RST,SW2,SW_Push_1P1T_XKB_TS-1187A,C318884,XKB,TS-1187A-B-A-B,1,Basic,951682,2026-11-06 07:12 UTC
TPS63900DSKR,U1,WSON-10-1EP_2.5x2.5mm_P0.5mm_EP1.2x2mm,C1518762,Texas Instruments,TPS63900DSKR,1,Extended,10729,2026-11-06 07:12 UTC
TPS3839K33DBZR,U3,SOT-23,C96333,Texas Instruments,TPS3839K33DBZR,1,Extended,745,2026-11-06 07:12 UTC
ESP32-H2FH4S,U4,QFN-32-1EP_4x4mm_P0.4mm_EP2.9x2.9mm,C50392664,Espressif,ESP32-H2FH4S,1,Extended,0,2026-11-06 07:12 UTC
SHT40-AD1B-R3,U5,Sensirion_DFN-4_1.5x1.5mm_P0.8mm_SHT4x_NoCentralPad,C2848306,Sensirion,SHT40-AD1B-R3,1,Extended,15227,2026-11-06 07:12 UTC
"32.768kHz CL 12.5pF, ESR<=70k, 20ppm",Y1,Crystal_SMD_3215-2Pin_3.2x1.5mm,C32346,Seiko Epson,Q13FC13500004,1,Basic,488960,2026-11-06 07:12 UTC
"32MHz CL 9pF, +-10ppm, 40 ohm",Y2,Crystal_SMD_3225-4Pin_3.2x2.5mm,C5210649,YXC,X322532MLB4SI,1,Extended,3525,2026-11-06 07:12 UTC

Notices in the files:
parts and their libraries:
ESP32-H2 SoC, QFN32 4x4 mm (Espressif KiCad library, CC-BY-SA 4.0 with design exception)
